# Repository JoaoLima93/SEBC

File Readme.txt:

** Low Cost Embedded System for Dynamic Rate Simulation: Tarifa Branca **

This work aims to present a proposal for a system design compatible with electronic meters approved by INMETRO, which simulates the billing of White Rate customers, to assist them in the decision making of their tariff modality, since the implementation of the new model may cause doubts about its operation. In this way a low-cost electronic module will be proposed, applying the embedded system development methods for building the solution through the open source development platforms NodeMCU, KiCad, Lua Language, MySql and Android Studio.

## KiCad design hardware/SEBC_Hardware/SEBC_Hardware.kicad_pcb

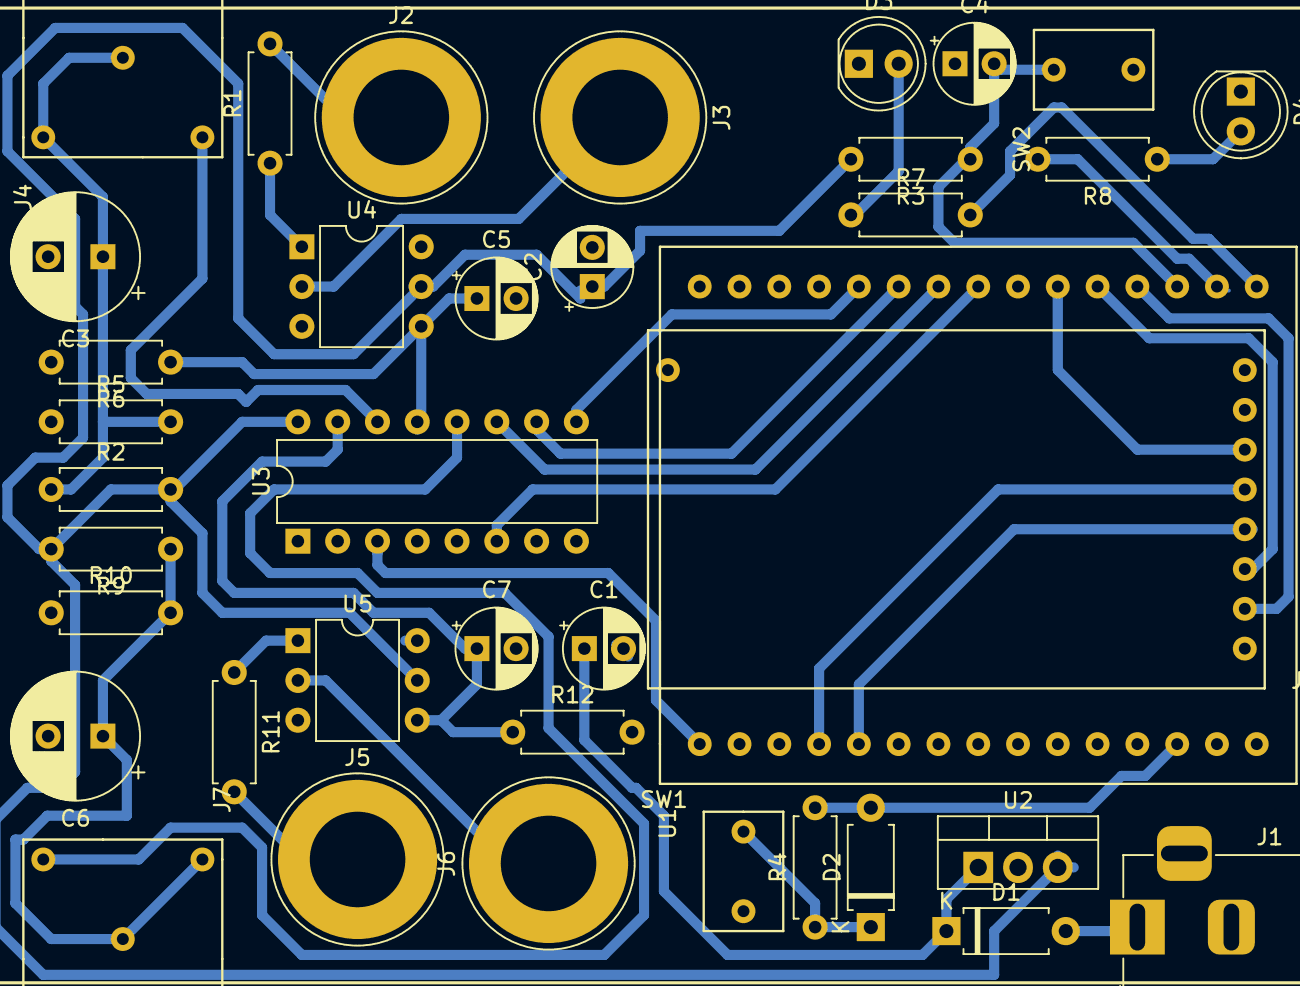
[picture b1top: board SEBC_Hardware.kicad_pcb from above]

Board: 2 copper layers, 38 parts (0 on the bottom side), 33 nets.

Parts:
C1, C2, C5, C7: 10uF; CP_Radial_D5.0mm_P2.50mm
C3, C6: 100 uF; CP_Radial_D8.0mm_P3.50mm
C4: 100 n; CP_Radial_D5.0mm_P2.50mm
D1: D_Zener_ALT; D_A-405_P7.62mm_Horizontal
D2: DIODE; D_A-405_P7.62mm_Horizontal
D3, D4: LED_ALT; LED_D5.0mm
J1: Barrel_Jack_Switch; BarrelJack_Horizontal
J2, J3, J5, J6: Conn_01x01_Female; Banana_Jack_1Pin
J4, J7: AudioJack2_Ground_Switch; JACKAUDIO_P2
J8: Micro_SD_Card; microSD
R1, R11: 220k; R_Axial_DIN0207_L6.3mm_D2.5mm_P7.62mm_Horizontal
R2, R4, R5, R9, R10: 10 k; R_Axial_DIN0207_L6.3mm_D2.5mm_P7.62mm_Horizontal
R3: 1k; R_Axial_DIN0207_L6.3mm_D2.5mm_P7.62mm_Horizontal
R6, R12: 10k; R_Axial_DIN0207_L6.3mm_D2.5mm_P7.62mm_Horizontal
R7, R8: 1 k; R_Axial_DIN0207_L6.3mm_D2.5mm_P7.62mm_Horizontal
SW1, SW2: SW_Push; push_button
U1: NodeMCU1.0(ESP-12E); nodmcu
U2: L7805; TO-220-3_Vertical
U3: 4051; DIP-16_W7.62mm
U4, U5: 4N25; DIP-6_W7.62mm

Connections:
+3V3: J8.6, U1.25
+5V: C2.1, R2.2, R3.2, R9.2, U1.15, U2.3, U3.16, U4.5, U5.5
/A0: U1.22, U3.11
/A1: U1.21, U3.10
/A2: U1.20, U3.9
/Boot: C4.2, R3.1, SW2.1, U1.28
/INN_E: U1.23, U3.6
/LED_01: R7.2, U1.30
/LED_02: R8.2, U1.29
/Reset: D2.2, R4.2, U1.13
/SD1: J8.2, U1.27
/SD2: J8.3, U1.26
/SD3: J8.4, U1.5
/SD4: J8.5, U1.4
/SENSOR_C_A: J4.S, U3.14
/SENSOR_C_B: J7.S, U3.12
/SENSOR_T_A: C5.1, R6.1, U3.13, U4.4
/SENSOR_T_B: C7.1, R12.1, U3.15, U5.4
/S_MUX: U1.1, U3.3
GND: C1.2, C2.2, C3.2, C4.1, C5.2, C6.2, C7.2, D3.1, D4.1, J1.2, J1.3, R5.1, R6.2, R10.1, R12.2, SW1.2, SW2.2, U1.14, U2.2, U3.7, U3.8
unnamed: C1.1, D1.1, U2.1
unnamed: C3.1, J4.T, J4.TN, R2.1, R5.2
unnamed: C6.1, J7.T, J7.TN, R9.1, R10.2
unnamed: D1.2, J1.1
unnamed: D2.1, R4.1, SW1.1
unnamed: D3.2, R7.1
unnamed: D4.2, R8.1
unnamed: J2.1, R1.2
unnamed: J3.1, U4.2
unnamed: J5.1, R11.2
unnamed: J6.1, U5.2
unnamed: R1.1, U4.1
unnamed: R11.1, U5.1

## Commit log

2018-06-19 :tada: Firmware SEBC 1.0
    Initial commit.
2018-06-19 :fire: Organização de Arquivos
2018-06-19 :speech_balloon: Cabeçalho do Código
2018-06-19 :memo: Readme
2018-06-20 :construction: Add HTML string in Nodmcu
2018-06-20 :sparkles: Include a button
2018-06-20 :art: Improving format of the code
2018-06-20 :fire: Delete code
2018-06-20 :fire: Delete Library
2018-06-20 :construction: Crate a submit button
2018-06-20 :construction: Submit button
2018-06-20 :sleeping: Coding almost asleep
2018-06-26 :art: Change structure
2018-07-09 :sparkles: MySQL Connection
2018-07-09 :fire: Delete txt
2018-07-09 :building_construction: Update Php files
2018-07-09 :bug: Fix conection bug
2018-07-09 :construction_worker: Salvat.php
2018-07-09 :sparkles: Include Senser
2018-07-17 :sparkle: New Client
2018-07-24 :computer: Add kicad hardware project
2018-07-24 :memo: Add Lista de componentes
2018-07-24 :electric_plug: Add sensor
2018-07-25 :electric_plug: Add mews plugs
2018-07-27 :memo: Lista de Componente
2018-07-27 :book: ESP8266 Kicad Library
2018-07-27 :construction: Adicionando MicroSD
2018-07-27 :memo: Lista de Componente
2018-07-29 :construction_worker: PCB
2018-07-29 :construction: SEBC PCB
2018-08-03 :zap: ADD `PCB
2018-08-03 :zap: Improving PCB performance
2018-10-12 :sparkle: Adicionando Mutiplexador
2018-10-12 :sparkle: Adicionando Leds de comunicação
2018-10-12 :sparkle: Adicionando leitura de multiplas fases
2018-10-12 :sparkle: Adicionando leitura de corrente
2018-11-16 :iphone: Add android app
2018-11-17 :iphone: Finalização do Login
2018-11-29 :sparkle: Add Cadastro de usuario
2018-12-01 :sparkle: Add Login
2018-12-18 :construction_worker: Work in Progress
2019-01-14 :sparkle: Organizando API
2019-01-14 :white_check_mark: Incluido Teste de API
2019-01-14 :truck: Mudando nome da pasta
2019-01-15 :sparkle: Add listaTarifaAtual
2019-01-15 :sparkle: Add lista tarifas comuns
2019-01-15 :construction_worker: Add lista consumo comum por cliente
2019-01-17 :sparkle: Add APi de consumo
2019-01-18 :sparkle: Add Tipo de Rede
2019-01-18 :sparkle: Add deletar consumo e tarifa
2019-01-22 :robot: Include grafic to the app
2019-01-27 :sparkle: Firmware developed
2019-01-27 :sparkle: Adicionando versão 2.0
2019-01-28 :sparkle: API final version
2019-01-28 :sparkle: Firmware final version
2019-01-28 :white_check_mark: API test
2019-01-28 :card_file_box: Create Database events
2019-01-28 :card_file_box: Event activation
2019-01-28 :card_file_box: Correct event calculation
2019-01-29 :card_file_box: Create table in database
2019-02-03 :bug: Correct bug in real power
